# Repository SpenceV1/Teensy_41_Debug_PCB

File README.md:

# Teensy_41_Debug_PCB
Teensy 4.1 Debug PCB

This modification adds the ability to connect to a Teensy 4.1 device over JTAG with a Segger J-Link Debug Probe.

This PCB is only for the newest Teensy 4.1 with the GD32 bootloader chip.

The previous method has been depreciated, keeping the bootloader chip in place has proven to be much easier.

[Installation Instructions](https://docs.google.com/document/d/1ZLD2jC9SxiCBk1NZLw667Tu3JuIk6PAyAxSHW7cWvu8/edit?usp=sharing)

[OSHPARK](https://oshpark.com/shared_projects/GGq82uJN)

See [Teensy_41_Debug_Adapter](https://github.com/SpenceV1/Teensy_41_Debug_Adapter)

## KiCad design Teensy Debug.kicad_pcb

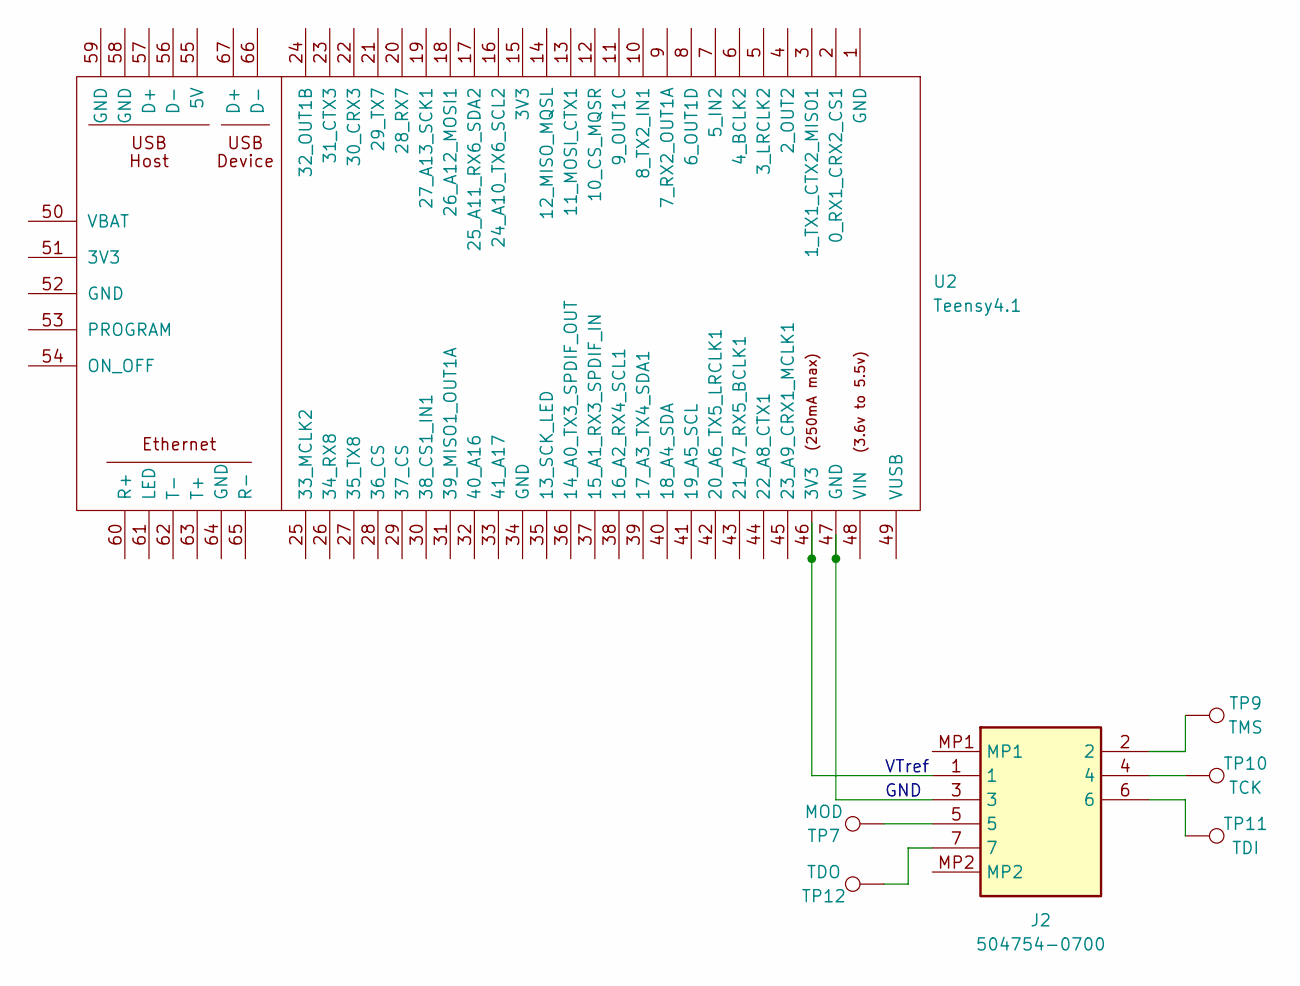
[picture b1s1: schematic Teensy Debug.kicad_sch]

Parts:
J2: 504754-0700; 5047540700; Mouser Part Number 538-504754-0700
TP7: MOD; Via 0.508 0.254 mm
TP9: TMS; Via 0.508 0.254 mm
TP10: TCK; Via 0.508 0.254 mm
TP11: TDI; Via 0.508 0.254 mm
TP12: TDO; Via 0.508 0.254 mm
U2: Teensy4.1; Teensy41

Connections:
unnamed: J2.1, U2.46 (3V3)
unnamed: J2.2, TP9.1
unnamed: J2.3, U2.47 (GND)
unnamed: J2.4, TP10.1
unnamed: J2.5, TP7.1
unnamed: J2.6, TP11.1
unnamed: J2.7, TP12.1

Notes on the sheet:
GND
VTref

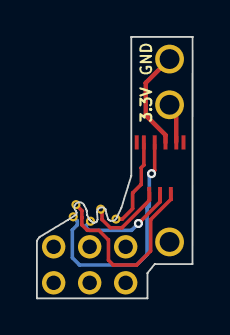
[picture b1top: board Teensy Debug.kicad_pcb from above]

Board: 2 copper layers, 8.7 x 14.5 mm, 7 parts (0 on the bottom side), 7 nets.

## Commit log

2021-06-28 V2
    Changed from generic header to Cortex-M 9 pin debug header.
2021-06-29 Changed through hole connection to surface mount
    Through hole connection has been replaced with surface mount pads in favor of hot air installation.
2021-06-29 Revision 5
    Added revision, middle ground pad resized, cleaned up a few wires, updated labels for readability.
2021-09-25 Mini Version
    Removed Cortex M0, replaced with Attiny10, flex pcb fits within the size of the Teensy 4.1
2022-01-05 V2 Mini
    Current version
2022-01-05 Schematic Labels
    Add labels to Teensy & MKL02
2023-07-16 Added 0.25mm to FPC Connector Pads
    Lengthened FPC connector pads outward by 0.25mm for easier soldering
2023-08-22 Update README.md
    Added link to installation instructions
2023-08-25 Update README.md
    Added OSHPARK link
2023-08-25 Update README.md
    Added Debug Adapter link
